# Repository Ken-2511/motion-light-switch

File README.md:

# Corridor Motion-Sensing Light Switch

A motion-activated light controller for school corridors in mainland China. A battery-powered **slave** sits on each existing wall switch and presses it with a small servo, so the device never touches 220 V mains. One USB-powered **master** commands all slaves over LoRa and serves a web page over WiFi. Top design priority: slave battery life.

**How to read this file:** Section 1 holds only decisions the author has confirmed. Section 2 lists open questions. Section 3 lists suggestions that are **not** confirmed. Section 4 is an estimate, not a measurement.

**Repository layout:**

| Folder | Contents |
| --- | --- |
| `slave/` | KiCad project `motion-light-switch-slave` (schematic and 50×80 mm PCB) |
| `master/` | KiCad project `motion-light-switch-master` (schematic and 46×34 mm PCB) |
| `lib/` | Shared KiCad library `motion-light-switch`: custom symbols (`motion-light-switch.kicad_sym`) and footprints (`motion-light-switch.pretty/`), used by both projects |

The two boards are ordered as separate designs (a combined panel would incur a different-design surcharge).

## 1. Confirmed Decisions

### 1.1 Site

| Item | Decision |
| --- | --- |
| Light | Existing 220 V AC corridor lights |
| Switch | Single-gang rocker; lower half = on, upper half = off |
| Switch panel | Believed to be the Chinese 86-type (86×86 mm plate). The rocker covers most of the plate: about 76 mm wide and 72 mm tall, leaving ~5 mm at each side (author's estimate; not yet measured). |
| Layout | Several switches along the corridor; each switch's lights cover a few meters |
| Foot traffic | Heavy during class breaks, arrival and dismissal; sparse otherwise |

### 1.2 System

| Item | Decision |
| --- | --- |
| Units | One master; one slave per switch |
| Radio protocol | Plain LoRa between master and slaves (not LoRaWAN) |
| Radio chip | Semtech SX1268 in both master and slave |
| Band | 433 MHz (433.05–434.79 MHz), transmit power ≤ 10 mW per MIIT micro-power rules. 470–510 MHz rejected: MIIT designates it mainly for civil metering devices. |
| Custom PCBs | Slave board, as small as possible; master carrier board for the ESP32-C3 SuperMini and the radio module |
| EDA | KiCad |

### 1.3 Control Logic

1. When a slave detects a person, it presses the switch to turn the light on and reports to the master.
2. Only the master decides when to turn a light off.
3. The slaves do not sense whether the light is actually on.
4. Daytime handling combines the slave's ambient-light reading with the master's time-of-day rules.
5. The master can command any slave at any time, for example turning on the lights at slaves next to one that detected motion. About 1 s from master command to slave action is acceptable.
6. Each slave listens using the SX1268's built-in duty-cycled receive (`SetRxDutyCycle`) with a period of about 1 s while its MCU sleeps. The master sends every packet with a preamble longer than that period.

### 1.4 Master

| Item | Decision |
| --- | --- |
| Hardware | 46×34 mm carrier PCB: an ESP32-C3 SuperMini plugs into two 1×8 2.54 mm sockets (rows 15.24 mm apart, USB-C at the top edge), and an Ebyte E22-400M22S (same module as the slave) is soldered on. 10 µF + 100 nF at the module's VCC, a keep-out under the module, two M3 mounting holes. |
| Radio supply | The SuperMini's 3V3 output |
| Power | USB, always on, placed near a power outlet |
| Network | Existing password-protected WiFi |
| Functions | Shows slave status and accepts commands from a phone; decides when lights turn off; applies time-of-day rules |
| Phone access | Same WiFi network only; no custom app |

**Master pin assignment (ESP32-C3 SuperMini):** strapping pins GPIO2, GPIO8 (on-board LED) and GPIO9 (BOOT button) are unused; logs go over the SuperMini's USB-C.

| GPIO | Use |
| --- | --- |
| GPIO6 / GPIO7 / GPIO5 | E22 SCK / MOSI / MISO |
| GPIO10 | E22 NSS |
| GPIO4 | E22 BUSY |
| GPIO3 | E22 DIO1 |
| GPIO20 | E22 NRST |
| GPIO0 / GPIO1 | E22 TXEN / RXEN |
| GPIO21 | Spare, on test pad TP1 |

The SuperMini pin order and row spacing come from a published pinout image; check them against the real board before ordering.

### 1.5 Slave Electronics

| Item | Decision |
| --- | --- |
| MCU | STM32L051K8T6 (Cortex-M0+, 64 KB flash, LQFP32). Chosen over the 32 KB STM32L031 for firmware headroom. |
| Radio | Ebyte E22-400M22S (SX1268, 14×20 mm, stamp holes, TCXO) on SPI |
| Antenna | 433 MHz FPC antenna (e.g. TX433-FPC-3208) plugged into the module's own IPEX socket; the module's ANT pad is left unconnected and the slave PCB has no antenna connector |
| Battery | One 18650 cell, removed and charged in an external charger |
| Battery holder | Generic 1-cell through-hole 18650 holder from Taobao, a clone of the MPD BH-18650-PC (77.7 mm long; solder pins 72.90 mm apart; two Ø3.2 mm mounting holes 55.61 mm apart). Soldered onto the slave PCB with KiCad footprint `Battery:BatteryHolder_MPD_BH-18650-PC`, whose pad 1 is +. The genuine MPD part (LCSC C5339083) was out of stock. |
| Reverse-polarity protection | AO3401 P-MOSFET: drain to battery +, source to the circuit, gate to ground through a resistor. Chosen over a diode to avoid a ~0.3 V drop. |
| 3.3 V regulator | TPS7A0233 (fixed 3.3 V, ~25 nA quiescent current, SOT-23-5). Powers the MCU, radio and sensors only (~30 mA peak). |
| Servo | MG90S (metal gears, ~2.2 kg·cm, same size as the SG90). Stall current up to ~1 A, which the servo power switch and the 18650 handle. |
| Servo power switch | High-side P-MOSFET from the battery, off whenever the servo is idle. A ~100 kΩ resistor pulls its gate up to the battery; a 2N7002 driven by the MCU pulls it low. |
| Servo supply voltage | Directly from the battery (~3.0–4.2 V) through the servo power switch. The current PCB has no boost converter; if the bench test shows the servo needs 5 V, the board needs a revision. |
| Motion sensor | Bare AM312 PIR (LCSC C114881, TO-5 can; pins 1 VDD, 2 OUT, 3 GND per LCSC) soldered on the PCB, behind a separate Fresnel lens in the enclosure. mmWave rejected for its current draw. Current: ~13–15 µA measured by others at 3.3 V; datasheet maximum 0.1 mA. |
| PIR power switching | PIR powered from PA8 through a 100 Ω / 1 µF filter, so firmware can switch it off when lights are not needed (daytime, weekends, holidays). Firmware ignores PIR_OUT for ~30 s after power-up and keeps PA0's pull-up off while the PIR is off. |
| Ambient light | Everlight ALS-PT19-315C/L177/TR8 visible-light phototransistor (LCSC C146233, 0603), read by the ADC with a 100 kΩ load and powered from a GPIO only while measuring. Chosen over the infrared PT15-21C, which barely sees LED lighting. |
| Battery monitoring | No extra parts. Firmware measures VDD with the internal voltage reference; VDD follows the battery once it falls below ~3.3 V. This gives a low-battery warning only, not a full-range gauge. |
| Status LED | Shows pairing, low battery and motion trigger |
| External button | User function, e.g. pause this slave for 2 hours |
| Internal button | Pairing and debug; not reachable from outside |
| Clock | 32.768 kHz crystal on the LSE pins for accurate timers (under 1 µA). The internal LSI RC oscillator (26–56 kHz) was rejected as too inaccurate. |
| Crystal | HCI FC31M2-32.768-N07LLDTL (LCSC C5120558): 3215 package, 7 pF load, ±20 ppm, ESR < 70 kΩ, with two 10 pF capacitors. Its ESR needs the STM32's medium-high LSE drive (LSEDRV = 10); firmware must set this before enabling the LSE. Chosen because the lower-ESR Epson FC-135R was out of stock. Drop-in alternative: ECS-.327-7-34R-TR (LCSC C6547871, ESR 50 kΩ, medium-low drive), only 5 in stock on 2026-11-11. |
| Firmware updates | SWD programming pads; no OTA |

### 1.6 Slave Pin Assignment (STM32L051K8T6)

Checked against ST datasheet DS10184 Rev 10. PA0–PA3 each use their own EXTI line, so all four can wake the MCU from Stop mode.

| Pin | Use | Notes |
| --- | --- | --- |
| PA0 | PIR output | EXTI0 |
| PA1 | SX1268 DIO1 | EXTI1 |
| PA2 | External button | EXTI2 |
| PA3 | Internal button | EXTI3 |
| PA4 | SX1268 NSS | Chip select |
| PA5 / PA6 / PA7 | SX1268 SCK / MISO / MOSI | SPI1 (AF0) |
| PB0 | SX1268 BUSY | Input |
| PB7 | SX1268 NRESET | Output |
| PA11 / PA12 | SX1268 TXEN / RXEN | Connect only if the chosen module needs them |
| PA15 | Servo PWM | TIM2_CH1 (AF5) |
| PB3 | Spare PWM | TIM2_CH2 (AF2), for a future double-gang version |
| PB6 | Servo power enable | Gate of the 2N7002 |
| PB1 | Phototransistor signal | ADC_IN9 |
| PB5 | Phototransistor power | High only while measuring |
| PB4 | Status LED | |
| PA9 / PA10 | Debug UART TX / RX | USART1 (AF4) |
| PA13 / PA14 | SWDIO / SWCLK | Programming pads |
| PC14 / PC15 | 32.768 kHz crystal (LSE) | HCI FC31M2, 7 pF load, with 10 pF caps |
| PA8 | PIR power (PIR_PWR) | Through a 100 Ω / 1 µF filter |
| BOOT0 (pin 31) | Boot mode | 10 kΩ pull-down to ground, so the chip always runs user firmware |
| NRST (pin 4) | Reset | To the reset button and the SWD pads |

Firmware must configure PB9, PB12–PB15, PH0, PH1 and PC13 as outputs driven low. These exist inside the chip but have no pins on LQFP32, and the datasheet requires this.

### 1.7 Slave Enclosure

| Item | Decision |
| --- | --- |
| Construction | Two pieces. A backplate sticks to the wall with removable double-sided adhesive; the main body clips onto it. |
| Tamper resistance | Hidden hex screw on the bottom, against children |
| Maintenance | Remove the main body to swap the battery |
| Fabrication | 3D printed (author has a printer) |
| Press mechanism | A straight printed bar, ~66 mm long and ~6 mm wide, fixed at its middle to the servo shaft through a printed hub (~8 mm long). The shaft runs parallel to the wall at the rocker's pivot height, so the bar stands in front of the rocker like a second seesaw: tilting it ~10–15° one way presses one end of the rocker while the bar's other end backs away. The bar sits over the rocker's left edge, with its ends ~33 mm from the pivot; the servo body sits just outside the plate. At rest the bar is centered with a few millimeters of gap at both ends, so the rest of the rocker can still be pressed by hand. |
| Extra force, if needed | A 10-tooth to 30-tooth spur gear pair between servo and bar (3× force, 1/3 speed), added only if the force test shows the servo alone is too weak |

## 2. Open Questions

- [ ] Whether the MG90S works reliably straight from the battery down to ~3.0 V (bench test)
- [ ] Force needed to flip the switch, pressing one rocker end ~33 mm from the pivot (e.g. with a kitchen scale). The MG90S with the bar gives roughly 5 N at 3.7 V; above ~3 N needed, add the gear pair.
- [ ] Whether pressing near one edge twists the wide rocker
- [ ] Boost converter IC and a board revision, if the bench test shows 5 V is needed
- [ ] Motion-to-light-on latency target
- [ ] Light-off delay and report interval
- [ ] Phone side: master-hosted web page, Mi Home, or another platform
- [ ] Switch panel dimensions (measure): rocker size, plate thickness, and how far each rocker end sticks out
- [ ] Number of slaves

## 3. Unconfirmed Suggestions

| Area | Suggestion | Reason |
| --- | --- | --- |
| Parts | Boost IC with an enable pin | Can be shut off between servo actions |
| Mechanical | Servo pushes toward the wall, so the reaction force goes through the enclosure into the wall | The press cannot pry the unit off its adhesive |
| Mechanical | Locating pins on the backplate | Servo returns to the same position after reassembly |
| Firmware | Turn the light off locally if the master is unreachable for a long time | Lights do not stay on when the master fails |
| Firmware | Configurable servo direction | Some switches may be installed upside down |
| Firmware | While the light is on, report at most every 1/3 of the off-delay | Fewer wake-ups |
| Firmware | Off-delay slightly longer than a class break | One break causes one on/off cycle |
| Firmware | Measure ambient light only while the light is off | Otherwise the sensor reads the lamp |
| Firmware | Below ~3.0 V, stop driving the servo and report low battery | Prevents over-discharge |
| Firmware | LoRa ACK with random-backoff retransmission | Reports from several slaves can collide |
| Firmware | Watchdog timer | A slave stuck awake drains the battery quickly |
| Phone | Master-hosted web page, mDNS name, and a fixed IP via router DHCP reservation | No app needed; some Android phones do not support mDNS |
| Tools | easyeda2kicad to import LCSC footprints; a PPK2-class meter to measure current | |

## 4. Slave Battery Life Estimate

One 3000 mAh 18650 (~2400 mAh usable) at ~4.5 mAh/day lasts about 500 days in theory. Plan on one battery swap per semester until current is measured.

| Item | Estimate |
| --- | --- |
| Sleep current (PIR ~15 µA, radio duty-cycled receive ~10–20 µA, MCU, regulator and crystal ~2 µA) | ~25–40 µA (~0.6–1.0 mAh/day) |
| One on + off cycle (two servo presses) | ~0.13 mAh |
| One report to the master | ~0.01 mAh |
| School day (~25 on/off cycles, at most one report per minute while a light is on) | ~6 mAh/day |
| Weekend or holiday | ~1 mAh/day |
| Average | ~4.5 mAh/day |

Largest consumers, in order: servo presses, reports while a light is on, sleep current.

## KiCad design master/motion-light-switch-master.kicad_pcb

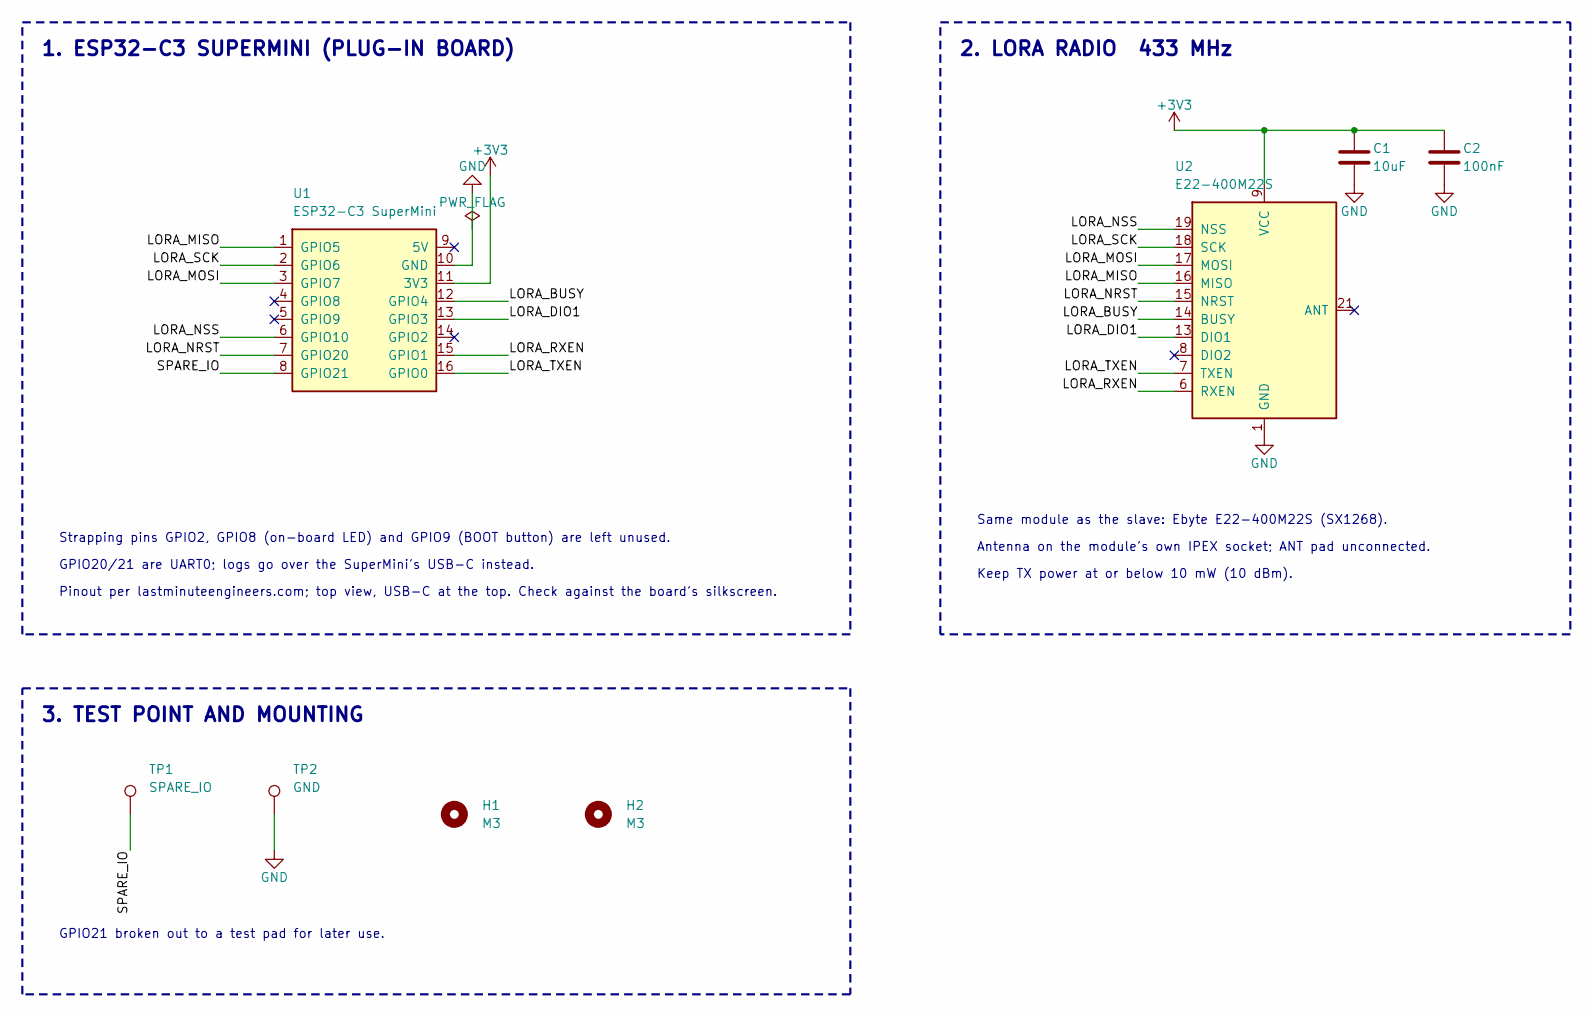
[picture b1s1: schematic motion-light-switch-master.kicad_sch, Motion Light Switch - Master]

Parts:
C1: 10uF; C_0805_2012Metric
C2: 100nF; C_0603_1608Metric
H1, H2: M3; MountingHole_3.2mm_M3
TP1: SPARE_IO; TestPoint_Pad_D1.0mm
TP2: GND; TestPoint_Pad_D1.0mm
U1: ESP32-C3 SuperMini; ESP32-C3_SuperMini_Socket
U2: E22-400M22S

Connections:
+3V3: C1.1, C2.1, U1.11 (3V3), U2.9 (VCC)
/LORA_BUSY: U1.12 (GPIO4), U2.14 (BUSY)
/LORA_DIO1: U1.13 (GPIO3), U2.13 (DIO1)
/LORA_MISO: U1.1 (GPIO5), U2.16 (MISO)
/LORA_MOSI: U1.3 (GPIO7), U2.17 (MOSI)
/LORA_NRST: U1.7 (GPIO20), U2.15 (NRST)
/LORA_NSS: U1.6 (GPIO10), U2.19 (NSS)
/LORA_RXEN: U1.15 (GPIO1), U2.6 (RXEN)
/LORA_SCK: U1.2 (GPIO6), U2.18 (SCK)
/LORA_TXEN: U1.16 (GPIO0), U2.7 (TXEN)
/SPARE_IO: TP1.1, U1.8 (GPIO21)
GND: C1.2, C2.2, TP2.1, U1.10 (GND), U2.1 (GND), U2.2 (GND), U2.3 (GND), U2.4 (GND), U2.5 (GND), U2.10 (GND), U2.11 (GND), U2.12 (GND), U2.20 (GND), U2.22 (GND)

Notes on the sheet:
1. ESP32-C3 SUPERMINI (PLUG-IN BOARD)
Strapping pins GPIO2, GPIO8 (on-board LED) and GPIO9 (BOOT button) are left unused.
GPIO20/21 are UART0; logs go over the SuperMini's USB-C instead.
Pinout per lastminuteengineers.com; top view, USB-C at the top. Check against the board's silkscreen.
2. LORA RADIO 433 MHz
Same module as the slave: Ebyte E22-400M22S (SX1268).
Antenna on the module's own IPEX socket; ANT pad unconnected.
Keep TX power at or below 10 mW (10 dBm).
3. TEST POINT AND MOUNTING
GPIO21 broken out to a test pad for later use.

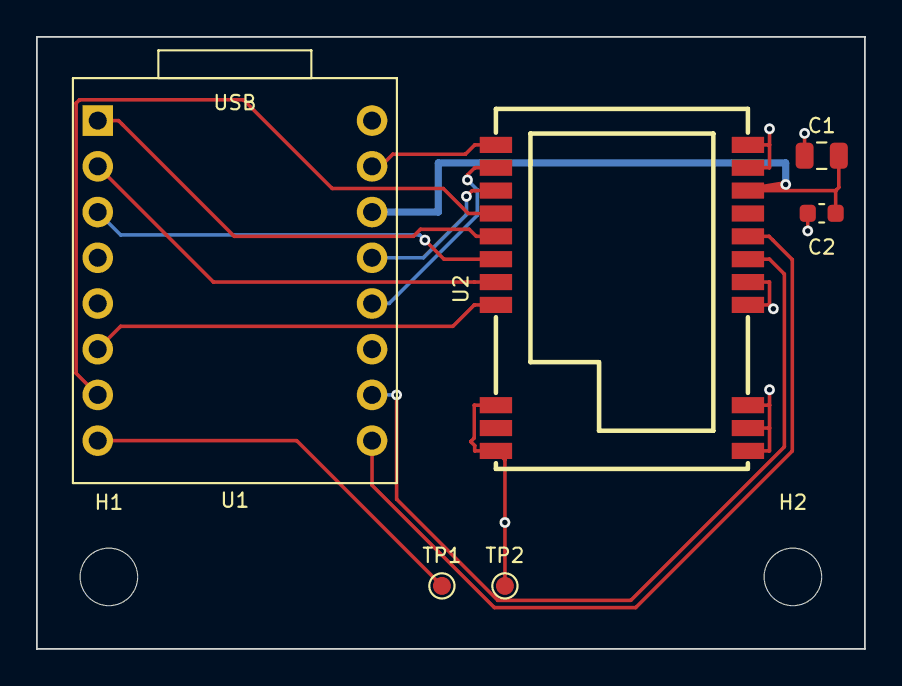
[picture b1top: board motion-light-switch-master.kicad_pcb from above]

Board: 2 copper layers, 46.0 x 34.0 mm, 8 parts (0 on the bottom side), 12 nets.

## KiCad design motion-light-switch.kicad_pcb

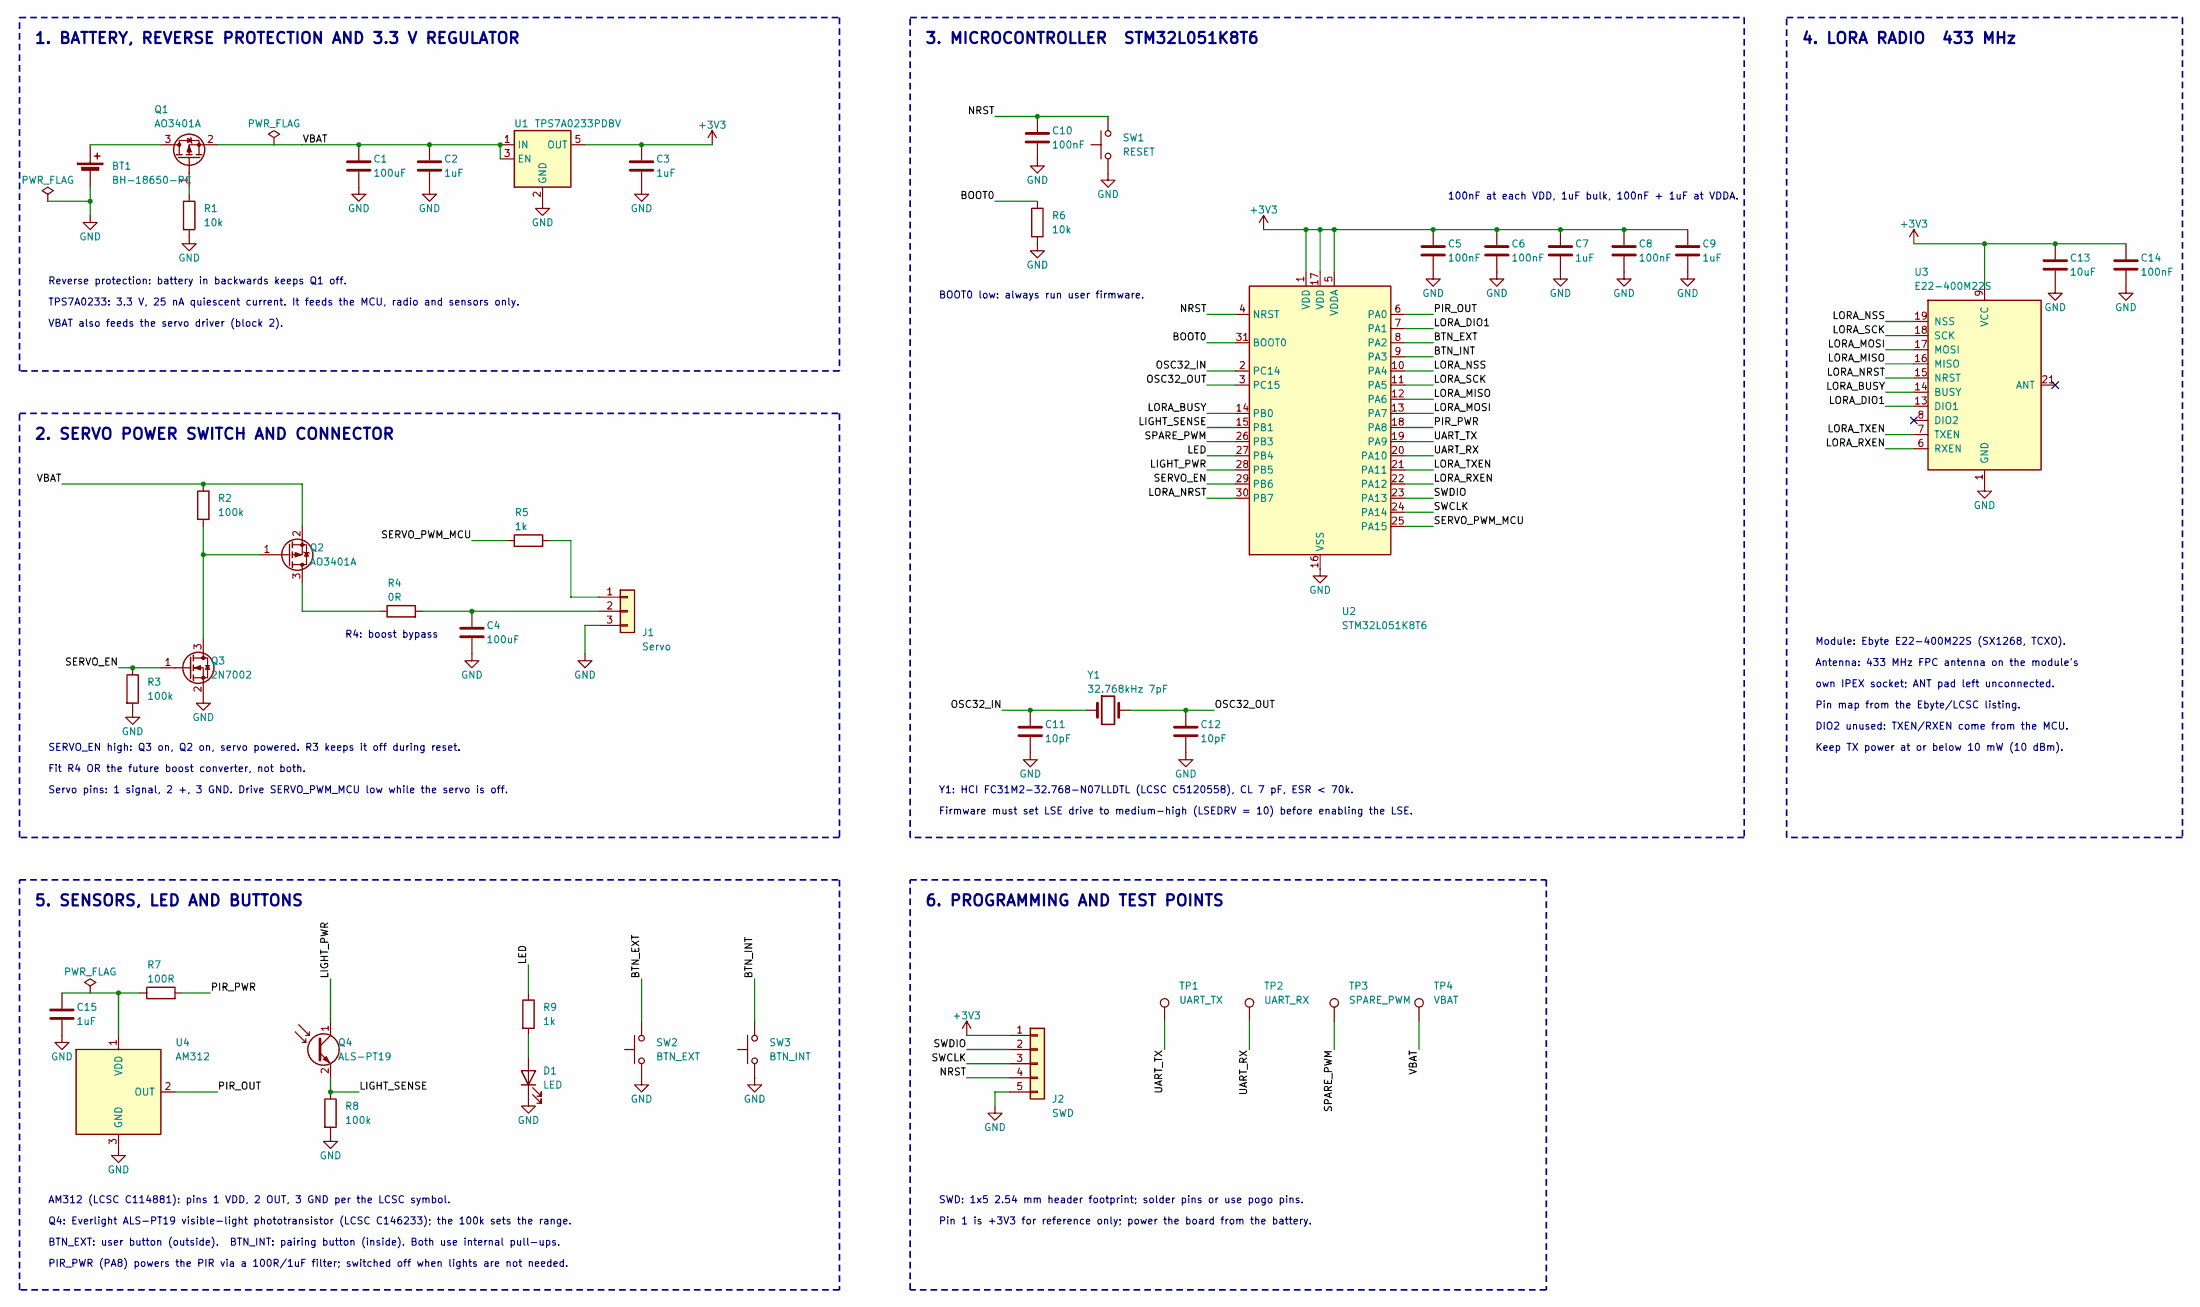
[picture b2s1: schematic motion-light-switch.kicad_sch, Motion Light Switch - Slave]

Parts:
BT1: BH-18650-PC; BatteryHolder_MPD_BH-18650-PC
C1, C4: 100uF; C_1206_3216Metric
C2, C3, C7, C9, C15: 1uF; C_0603_1608Metric
C5, C6, C8, C10, C14: 100nF; C_0603_1608Metric
C11, C12: 10pF; C_0603_1608Metric
C13: 10uF; C_0805_2012Metric
D1: LED; LED_0603_1608Metric
J1: Servo; PinHeader_1x03_P2.54mm_Vertical
J2: SWD; PinHeader_1x05_P2.54mm_Vertical
Q1, Q2: AO3401A; SOT-23
Q3: 2N7002; SOT-23
Q4: ALS-PT19
R1, R6: 10k; R_0603_1608Metric
R2, R3, R8: 100k; R_0603_1608Metric
R4: 0R; R_0603_1608Metric
R5, R9: 1k; R_0603_1608Metric
R7: 100R; R_0603_1608Metric
SW1: RESET; SW_SPST_TL3342
SW2: BTN_EXT; SW_SPST_TL3342
SW3: BTN_INT; SW_SPST_TL3342
TP1: UART_TX; TestPoint_Pad_D1.0mm
TP2: UART_RX; TestPoint_Pad_D1.0mm
TP3: SPARE_PWM; TestPoint_Pad_D1.0mm
TP4: VBAT; TestPoint_Pad_D1.0mm
U1: TPS7A0233PDBV; SOT-23-5
U2: STM32L051K8T6; LQFP-32_7x7mm_P0.8mm
U3: E22-400M22S
U4: AM312; AM312_TO-5-3
Y1: 32.768kHz 7pF; Crystal_SMD_3215-2Pin_3.2x1.5mm

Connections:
+3V3: C3.1, C5.1, C6.1, C7.1, C8.1, C9.1, C13.1, C14.1, J2.1, U1.5 (OUT), U2.1 (VDD), U2.5 (VDDA), U2.17 (VDD), U3.9 (VCC)
/BOOT0: R6.1, U2.31 (BOOT0)
/BTN_EXT: SW2.2, U2.8 (PA2)
/BTN_INT: SW3.2, U2.9 (PA3)
/LED: R9.1, U2.27 (PB4)
/LIGHT_PWR: Q4.1 (C), U2.28 (PB5)
/LIGHT_SENSE: Q4.2 (E), R8.1, U2.15 (PB1)
/LORA_BUSY: U2.14 (PB0), U3.14 (BUSY)
/LORA_DIO1: U2.7 (PA1), U3.13 (DIO1)
/LORA_MISO: U2.12 (PA6), U3.16 (MISO)
/LORA_MOSI: U2.13 (PA7), U3.17 (MOSI)
/LORA_NRST: U2.30 (PB7), U3.15 (NRST)
/LORA_NSS: U2.10 (PA4), U3.19 (NSS)
/LORA_RXEN: U2.22 (PA12), U3.6 (RXEN)
/LORA_SCK: U2.11 (PA5), U3.18 (SCK)
/LORA_TXEN: U2.21 (PA11), U3.7 (TXEN)
/NRST: C10.1, J2.4, SW1.2, U2.4 (NRST)
/OSC32_IN: C11.1, U2.2 (PC14), Y1.1
/OSC32_OUT: C12.1, U2.3 (PC15), Y1.2
/PIR_OUT: U2.6 (PA0), U4.2 (OUT)
/PIR_PWR: R7.2, U2.18 (PA8)
/SERVO_EN: Q3.1 (G), R3.1, U2.29 (PB6)
/SERVO_PWM_MCU: R5.1, U2.25 (PA15)
/SPARE_PWM: TP3.1, U2.26 (PB3)
/SWCLK: J2.3, U2.24 (PA14)
/SWDIO: J2.2, U2.23 (PA13)
/UART_RX: TP2.1, U2.20 (PA10)
/UART_TX: TP1.1, U2.19 (PA9)
/VBAT: C1.1, C2.1, Q1.2 (S), Q2.2 (S), R2.1, TP4.1, U1.1 (IN), U1.3 (EN)
GND: BT1.2 (-), C1.2, C2.2, C3.2, C4.2, C5.2, C6.2, C7.2, C8.2, C9.2, C10.2, C11.2, C12.2, C13.2, C14.2, C15.2, D1.1 (K), J1.3, J2.5, Q3.2 (S), R1.2, R3.2, R6.2, R8.2, SW1.1, SW2.1, SW3.1, U1.2 (GND), U2.16 (VSS), U2.32 (VSS), U3.1 (GND), U3.2 (GND), U3.3 (GND), U3.4 (GND), U3.5 (GND), U3.10 (GND), U3.11 (GND), U3.12 (GND), U3.20 (GND), U3.22 (GND), U4.3 (GND)
unnamed: BT1.1 (+), Q1.3 (D)
unnamed: D1.2 (A), R9.2
unnamed: J1.1, R5.2
unnamed: C4.1, J1.2, R4.2
unnamed: Q1.1 (G), R1.1
unnamed: Q2.3 (D), R4.1
unnamed: Q2.1 (G), Q3.3 (D), R2.2
unnamed: C15.1, R7.1, U4.1 (VDD)

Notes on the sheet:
1. BATTERY, REVERSE PROTECTION AND 3.3 V REGULATOR
Reverse protection: battery in backwards keeps Q1 off.
TPS7A0233: 3.3 V, 25 nA quiescent current. It feeds the MCU, radio and sensors only.
VBAT also feeds the servo driver (block 2).
2. SERVO POWER SWITCH AND CONNECTOR
R4: boost bypass
SERVO_EN high: Q3 on, Q2 on, servo powered. R3 keeps it off during reset.
Fit R4 OR the future boost converter, not both.
Servo pins: 1 signal, 2 +, 3 GND. Drive SERVO_PWM_MCU low while the servo is off.
3. MICROCONTROLLER STM32L051K8T6
100nF at each VDD, 1uF bulk, 100nF + 1uF at VDDA.
BOOT0 low: always run user firmware.
Y1: HCI FC31M2-32.768-N07LLDTL (LCSC C5120558), CL 7 pF, ESR < 70k.
Firmware must set LSE drive to medium-high (LSEDRV = 10) before enabling the LSE.
4. LORA RADIO 433 MHz
Module: Ebyte E22-400M22S (SX1268, TCXO).
Antenna: 433 MHz FPC antenna on the module's
own IPEX socket; ANT pad left unconnected.
Pin map from the Ebyte/LCSC listing.
DIO2 unused: TXEN/RXEN come from the MCU.
Keep TX power at or below 10 mW (10 dBm).
5. SENSORS, LED AND BUTTONS
AM312 (LCSC C114881): pins 1 VDD, 2 OUT, 3 GND per the LCSC symbol.
Q4: Everlight ALS-PT19 visible-light phototransistor (LCSC C146233); the 100k sets the range.
BTN_EXT: user button (outside). BTN_INT: pairing button (inside). Both use internal pull-ups.
PIR_PWR (PA8) powers the PIR via a 100R/1uF filter; switched off when lights are not needed.
6. PROGRAMMING AND TEST POINTS
SWD: 1x5 2.54 mm header footprint; solder pins or use pogo pins.
Pin 1 is +3V3 for reference only; power the board from the battery.

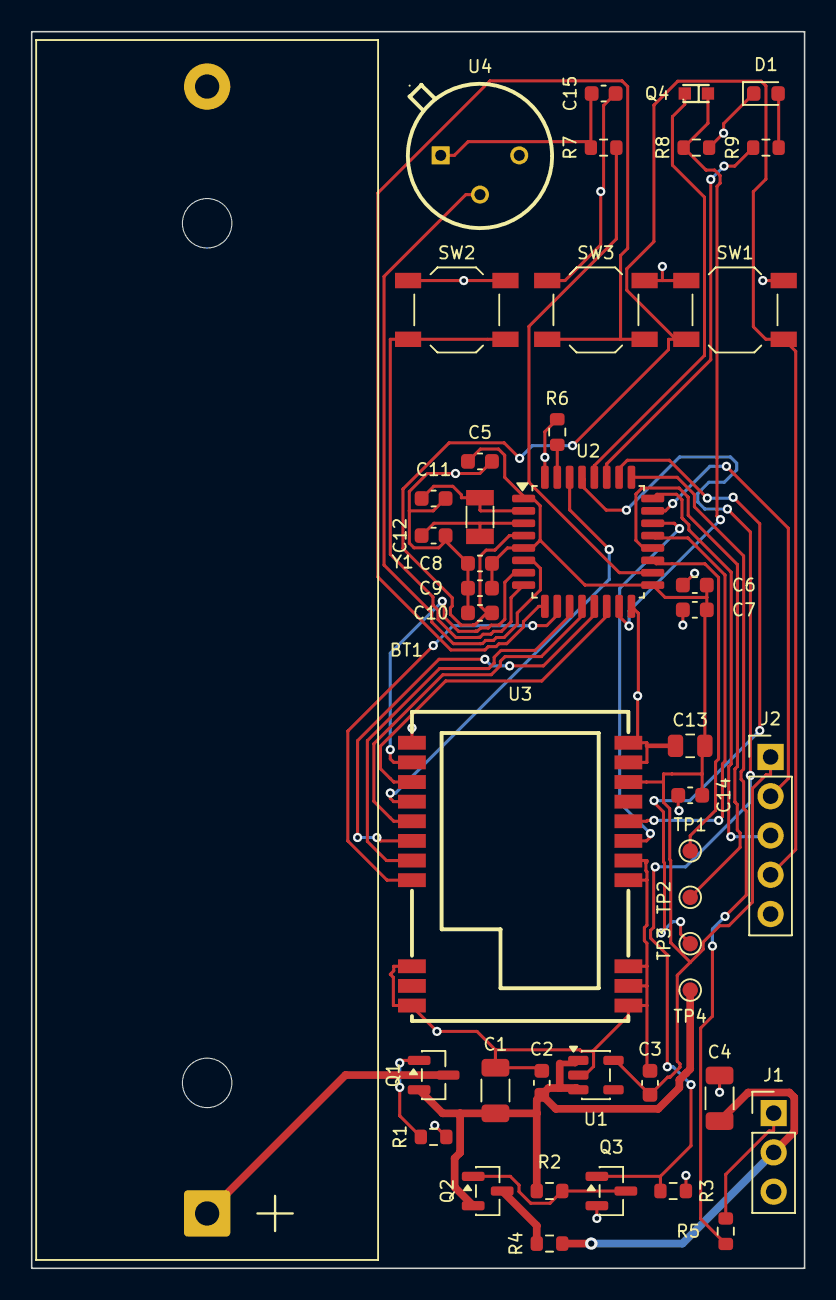
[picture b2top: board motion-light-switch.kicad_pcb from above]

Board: 2 copper layers, 50.0 x 80.0 mm, 44 parts (0 on the bottom side), 38 nets.
